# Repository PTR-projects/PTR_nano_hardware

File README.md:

# KPPTR-hardware

Welcome to the KPPTR-hardware repository! This repository contains the design files for the hardware components used in the KPPTR project. The design files have been created using KiCad 10.0, a powerful open-source electronics design automation suite.

## Project Overview

The design files in this repository correspond to the hardware components that make up the KPPTR project, which enhances the capabilities of DIY amateur rockets and high-altitude balloons. The design files have been crafted using KiCad 10.0, a popular and user-friendly tool for creating electronic schematics and PCB layouts. Both hardware and sofware were developed by PTR member!

## Design Files

The repository includes design files for the various hardware components used in the KPPTR project, including:

- **Schematics**: Detailed electronic schematics that illustrate the connections and components used in the design.
- **PCB Layouts**: PCB layout designs that define the placement and routing of components on the printed circuit board.
- **Libraries**: Custom component libraries and footprints used in the project.

## Getting Started

To access and work with the design files, follow these steps:

1. Clone the repository to your local machine.
2. Install [KiCad 10.0](https://www.kicad.org/download/) if you haven't already.
3. Open the KiCad project files (`.pro` files) in the appropriate subdirectories to access the schematics and PCB layouts.

Feel free to explore the design files and customize them to suit your specific needs. If you make any improvements or modifications to the hardware designs, consider contributing back to the repository to help the community.

## Contributors

- [bartekM](https://gitlab.com/space.tech)
- [https://gitlab.com/andrewziebinski](https://gitlab.com/andrewziebinski)
- [https://gitlab.com/Bdabrowsky](https://gitlab.com/Bdabrowsky)
- [https://gitlab.com/krecik1](https://gitlab.com/krecik1)
- [https://gitlab.com/US_air_force](https://gitlab.com/US_air_force)
- [https://gitlab.com/karmelek96](https://gitlab.com/karmelek96)
- and many others!

## License

This project is licensed under the [MIT License](LICENSE). You can freely use, modify, and distribute the code in accordance with the terms of the license.

Unless required by applicable law or agreed to in writing, this
software is distributed on an "AS IS" BASIS, WITHOUT WARRANTIES OR
CONDITIONS OF ANY KIND, either express or implied.

Thank you for your interest in KPPTR-firmware! If you have any questions or feedback, please don't hesitate to reach out to us. Happy coding and safe flights!

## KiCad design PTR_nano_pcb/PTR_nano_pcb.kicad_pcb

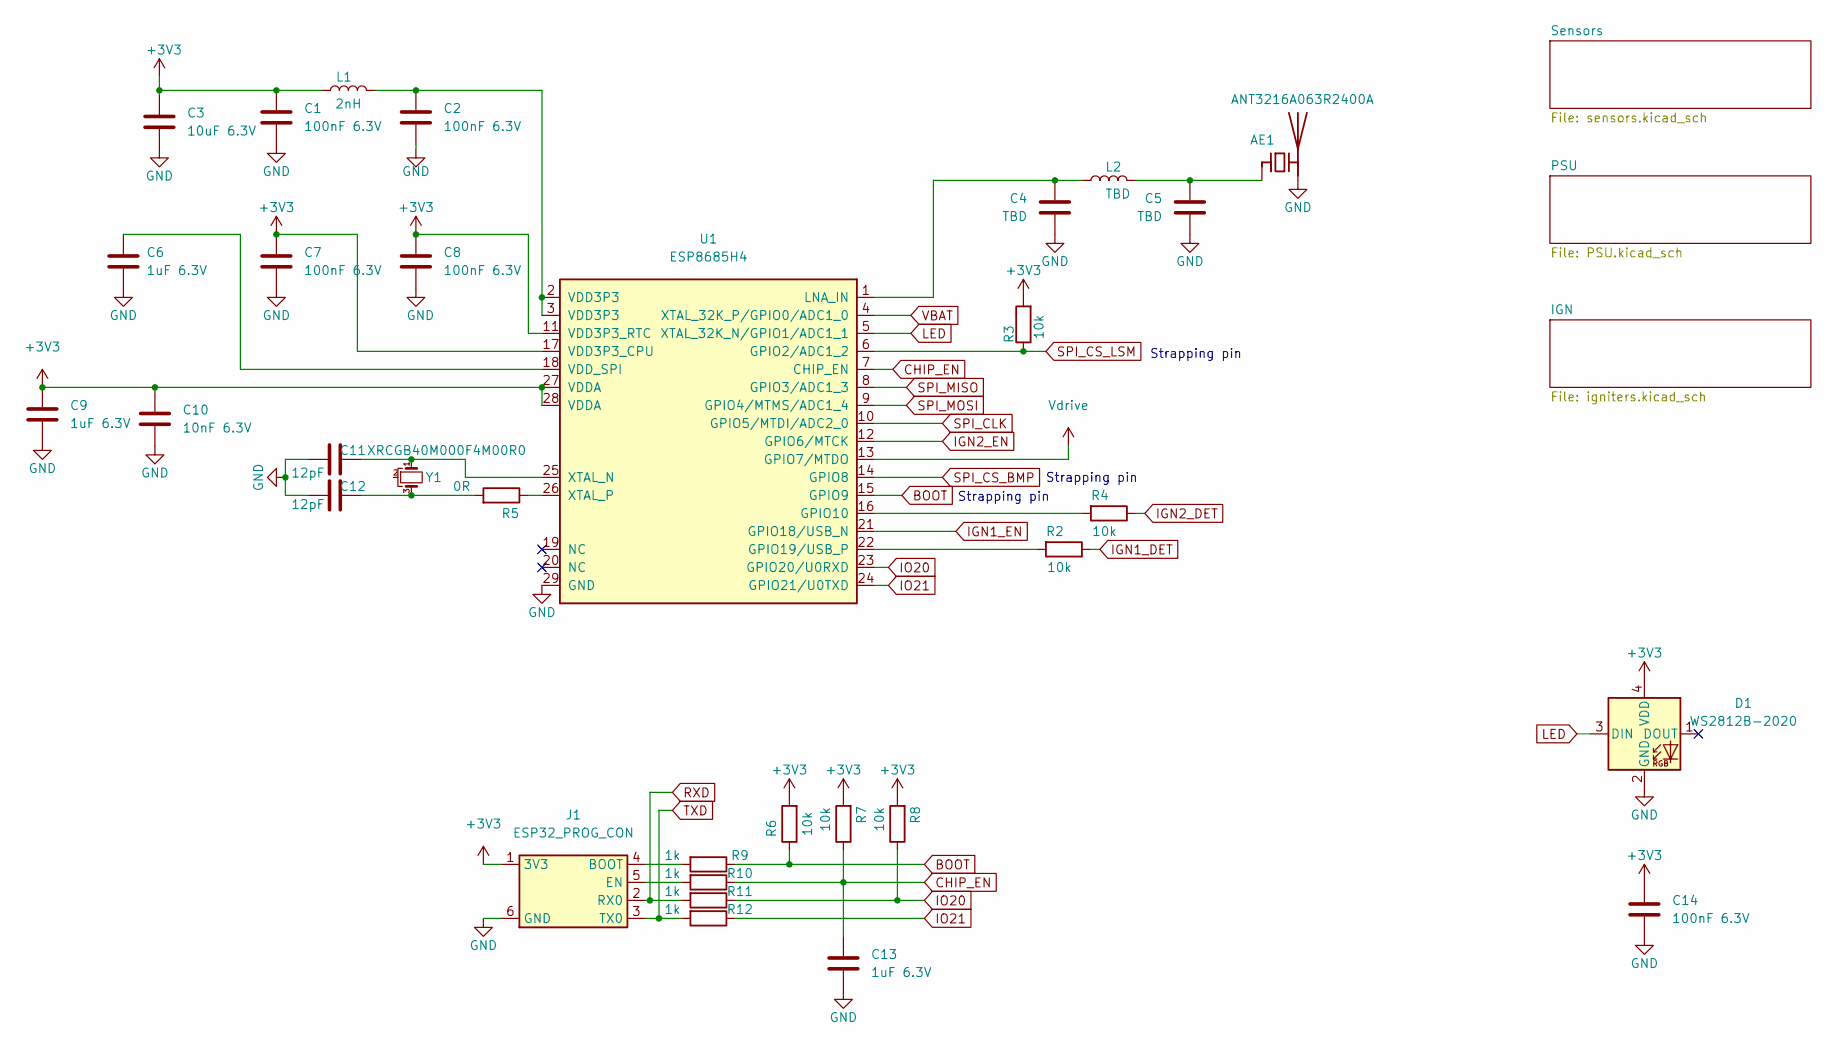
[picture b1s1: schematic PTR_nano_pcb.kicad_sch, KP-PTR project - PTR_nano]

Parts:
AE1: ANT3216A063R2400A
C1, C2, C7, C8, C14: 100nF 6.3V; C_0201_0603Metric
C3: 10uF 6.3V; C_0402_1005Metric
C4, C5: TBD; C_0201_0603Metric
C6, C9, C13: 1uF 6.3V; C_0201_0603Metric
C10: 10nF 6.3V; C_0201_0603Metric
C11, C12: 12pF; C_0201_0603Metric
D1: WS2812B-2020
J1: ESP32_PROG_CON; PinHeader_1x06_P1.27mm_Vertical
L1: 2nH; L_0201_0603Metric
L2: TBD; L_0201_0603Metric
R2, R3, R4, R6, R7, R8: 10k; R_0201_0603Metric
R5: 0R; R_0201_0603Metric
R9, R10, R11, R12: 1k; R_0201_0603Metric
U1: ESP8685H4; ESP8685; PARTREV 2.0
Y1: XRCGB40M000F4M00R0; Crystal_SMD_1612-4Pin_1.6x1.2mm

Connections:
+3V3: C1.1, C3.1, C7.1, C8.1, C9.1, C10.1, C14.1, D1.4 (VDD), J1.1 (3V3), L1.1, R3.2, R6.2, R7.2, R8.2, U1.11 (VDD3P3_RTC), U1.17 (VDD3P3_CPU), U1.27 (VDDA), U1.28 (VDDA); also elsewhere on the board
BOOT: R6.1, R9.1, U1.15 (GPIO9)
CHIP_EN: C13.1, R7.1, R10.1, U1.7 (CHIP_EN)
GND: AE1.2 (PCB_Trace), C1.2, C2.2, C3.2, C4.2, C5.2, C6.2, C7.2, C8.2, C9.2, C10.2, C11.1, C12.1, C13.2, C14.2, D1.2 (GND), J1.6 (GND), U1.29 (GND); also elsewhere on the board
IGN1_DET: R2.1; also elsewhere on the board
IGN1_EN: U1.21 (GPIO18/USB_N); also elsewhere on the board
IGN2_DET: R4.1; also elsewhere on the board
IGN2_EN: U1.12 (GPIO6/MTCK); also elsewhere on the board
IO20: R8.1, R11.1, U1.23 (GPIO20/U0RXD)
IO21: R12.1, U1.24 (GPIO21/U0TXD)
LED: D1.3 (DIN), U1.5 (XTAL_32K_N/GPIO1/ADC1_1)
unnamed: AE1.1 (FEED), C5.1, L2.1
unnamed: C2.1, L1.2, U1.2 (VDD3P3), U1.3 (VDD3P3)
unnamed: C12.2, R5.2, Y1.3
unnamed: J1.4 (BOOT), R9.2
unnamed: J1.5 (EN), R10.2
unnamed: R4.2, U1.16 (GPIO10)
unnamed: R2.2, U1.22 (GPIO19/USB_P)
unnamed: C4.1, L2.2, U1.1 (LNA_IN)
unnamed: C6.1, U1.18 (VDD_SPI)
unnamed: C11.2, U1.25 (XTAL_N), Y1.1
unnamed: R5.1, U1.26 (XTAL_P)
RXD: J1.2 (RX0), R11.2
SPI_CLK: U1.10 (GPIO5/MTDI/ADC2_0); also elsewhere on the board
SPI_CS_BMP: U1.14 (GPIO8); also elsewhere on the board
SPI_CS_LSM: R3.1, U1.6 (GPIO2/ADC1_2); also elsewhere on the board
SPI_MISO: U1.8 (GPIO3/ADC1_3); also elsewhere on the board
SPI_MOSI: U1.9 (GPIO4/MTMS/ADC1_4); also elsewhere on the board
TXD: J1.3 (TX0), R12.2
VBAT: U1.4 (XTAL_32K_P/GPIO0/ADC1_0); also elsewhere on the board
Vdrive: U1.13 (GPIO7/MTDO); also elsewhere on the board

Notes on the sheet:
Strapping pin

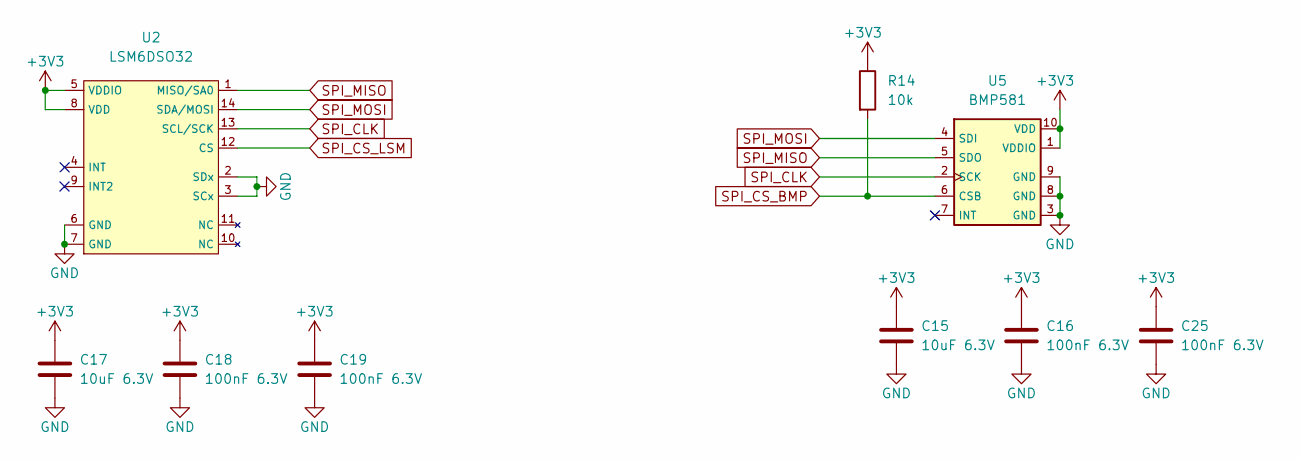
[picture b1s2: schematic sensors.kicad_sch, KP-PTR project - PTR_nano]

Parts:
C15, C17: 10uF 6.3V; C_0402_1005Metric
C16, C18, C19, C25: 100nF 6.3V; C_0201_0603Metric
R14: 10k; R_0201_0603Metric
U2: LSM6DSO32
U5: BMP581

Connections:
+3V3: C15.1, C16.1, C17.1, C18.1, C19.1, C25.1, R14.1, U2.5 (VDDIO), U2.8 (VDD), U5.1 (VDDIO), U5.10 (VDD); also elsewhere on the board
GND: C15.2, C16.2, C17.2, C18.2, C19.2, C25.2, U2.2 (SDx), U2.3 (SCx), U2.6 (GND), U2.7 (GND), U5.3 (GND), U5.8 (GND), U5.9 (GND); also elsewhere on the board
SPI_CLK: U2.13 (SCL/SCK), U5.2 (SCK); also elsewhere on the board
SPI_CS_BMP: R14.2, U5.6 (CSB); also elsewhere on the board
SPI_CS_LSM: U2.12 (CS); also elsewhere on the board
SPI_MISO: U2.1 (MISO/SA0), U5.5 (SDO); also elsewhere on the board
SPI_MOSI: U2.14 (SDA/MOSI), U5.4 (SDI); also elsewhere on the board

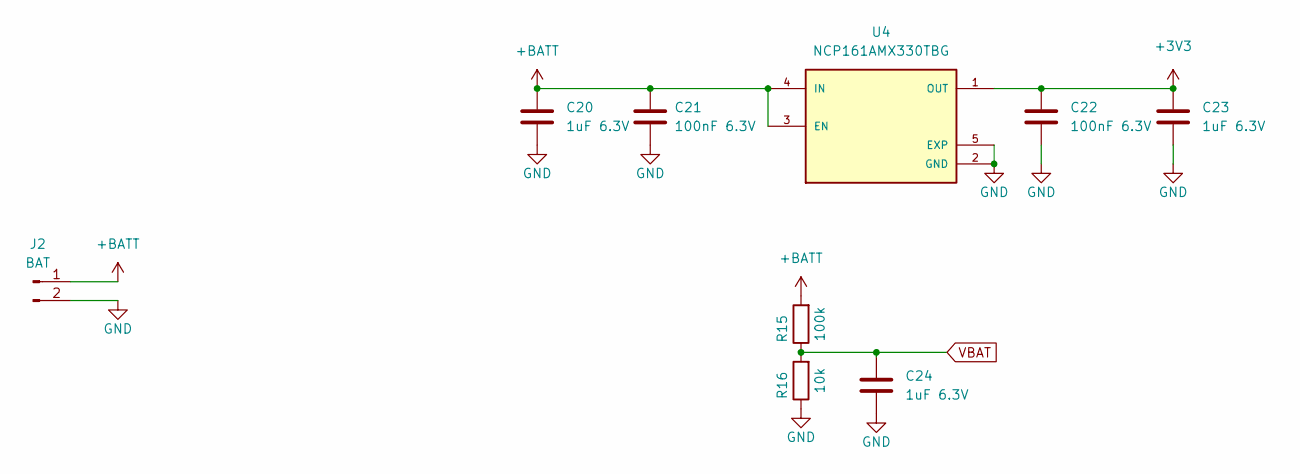
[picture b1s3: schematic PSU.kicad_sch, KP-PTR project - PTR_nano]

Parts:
C20, C23, C24: 1uF 6.3V; C_0201_0603Metric
C21, C22: 100nF 6.3V; C_0201_0603Metric
J2: BAT; Micro IGN-BAT pads
R15: 100k; R_0201_0603Metric
R16: 10k; R_0201_0603Metric
U4: NCP161AMX330TBG; PARTREV A

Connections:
+3V3: C22.1, C23.1, U4.1 (OUT); also elsewhere on the board
+BATT: C20.1, C21.1, J2.1, R15.2, U4.3 (EN), U4.4 (IN); also elsewhere on the board
GND: C20.2, C21.2, C22.2, C23.2, C24.2, J2.2, R16.1, U4.2 (GND), U4.5 (EXP); also elsewhere on the board
VBAT: C24.1, R15.1, R16.2; also elsewhere on the board

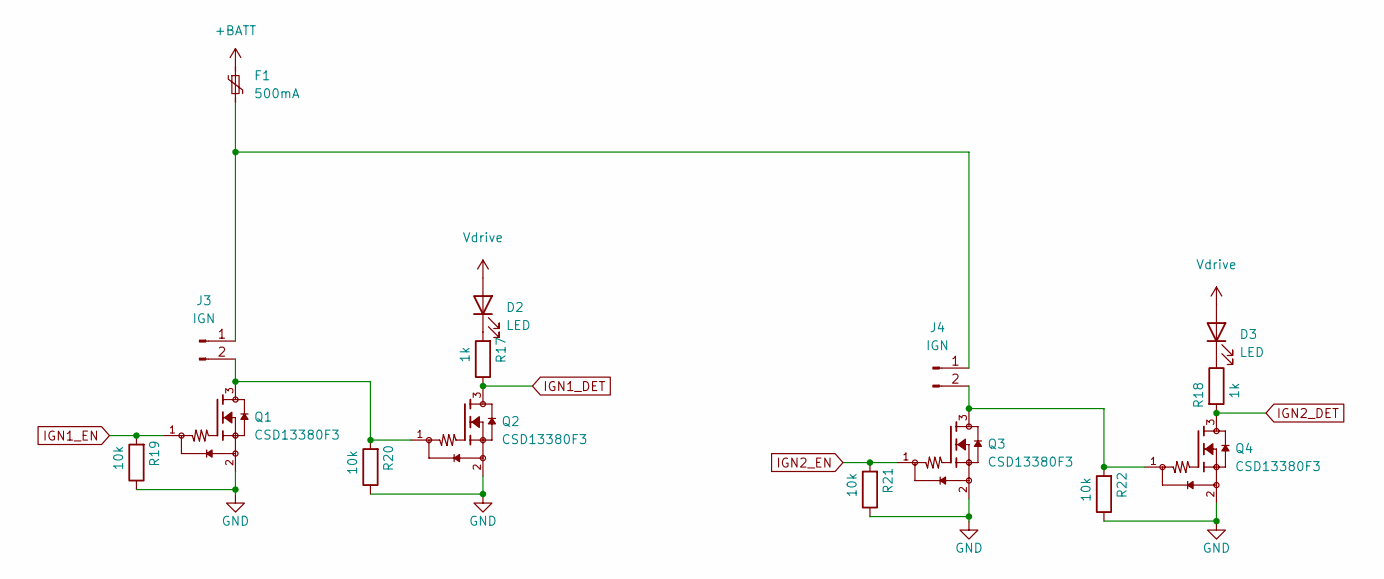
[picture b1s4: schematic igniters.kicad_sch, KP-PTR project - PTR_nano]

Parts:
D2, D3: LED; LED_0402_1005Metric
F1: 500mA; Fuse_0805_2012Metric
J3, J4: IGN; Micro IGN-BAT pads
Q1, Q2, Q3, Q4: CSD13380F3; PARTREV October 2016
R17, R18: 1k; R_0201_0603Metric
R19, R20, R21, R22: 10k; R_0201_0603Metric

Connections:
+BATT: F1.1; also elsewhere on the board
GND: Q1.2, Q2.2, Q3.2, Q4.2, R19.1, R20.1, R21.1, R22.1; also elsewhere on the board
IGN1_DET: Q2.3, R17.1; also elsewhere on the board
IGN1_EN: Q1.1, R19.2; also elsewhere on the board
IGN2_DET: Q4.3, R18.2; also elsewhere on the board
IGN2_EN: Q3.1, R21.2; also elsewhere on the board
unnamed: D2.1 (K), R17.2
unnamed: D3.1 (K), R18.1
unnamed: F1.2, J3.1, J4.1
unnamed: J3.2, Q1.3, Q2.1, R20.2
unnamed: J4.2, Q3.3, Q4.1, R22.2
Vdrive: D2.2 (A), D3.2 (A); also elsewhere on the board

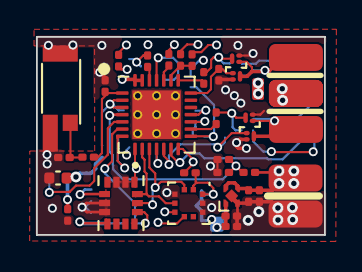
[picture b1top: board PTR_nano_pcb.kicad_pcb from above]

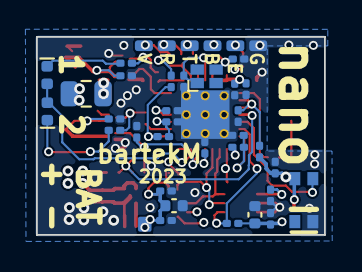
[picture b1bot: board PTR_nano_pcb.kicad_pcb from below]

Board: 6 copper layers, 16.0 x 11.0 mm, 65 parts (31 on the bottom side), 37 nets.

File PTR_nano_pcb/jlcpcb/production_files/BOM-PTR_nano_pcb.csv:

Comment,Designator,Footprint,LCSC,Quantity
0R,R5,R_0201_0603Metric,C100147,1
100k,R15,R_0201_0603Metric,C102685,1
100nF 6.3V,"C1,C14,C16,C18,C19,C2,C21,C22,C25,C7,C8",C_0201_0603Metric,C2833634,11
10k,"R14,R16,R19,R2,R20,R21,R22,R3,R4,R6,R7,R8",R_0201_0603Metric,C509700,12
10nF 6.3V,C10,C_0201_0603Metric,C309453,1
10uF 6.3V,"C15,C17,C3",C_0402_1005Metric,C15525,3
12pF,"C11,C12",C_0201_0603Metric,C384960,2
1k,"R10,R11,R12,R17,R18,R9",R_0201_0603Metric,C7467283,6
1uF 6.3V,"C13,C20,C23,C24,C6,C9",C_0201_0603Metric,C87143,6
2nH,L1,L_0201_0603Metric,C54929556,1
500mA,F1,Fuse_0805_2012Metric,C1017,1
ANT3216A063R2400A,AE1,ANT3216A063R2400A,C412135,1
BMP581,U5,BMP581,C5362283,1
CSD13380F3,"Q1,Q2,Q3,Q4",CSD13380F3,C2871092,4
ESP8685H4,U1,ESP8685,C4944062,1
LED,"D2,D3",LED_0402_1005Metric,C74338,2
LSM6DSO32,U2,LSM6DSO32,C22461202,1
NCP161AMX330TBG,U4,NCP161AMX330TBG,C892180,1
WS2812B-2020,D1,WS2812B-2020,C52917434,1
XRCGB40M000F4M00R0,Y1,Crystal_SMD_1612-4Pin_1.6x1.2mm,C1986027,1
TBD,C4,C_0201_0603Metric,,1
ESP32_PROG_CON,J1,PinHeader_1x06_P1.27mm_Vertical,,1
TBD,C5,C_0201_0603Metric,,1
TBD,L2,L_0201_0603Metric,,1
IGN,J3,Micro IGN-BAT pads,,1
IGN,J4,Micro IGN-BAT pads,,1
BAT,J2,Micro IGN-BAT pads,,1
